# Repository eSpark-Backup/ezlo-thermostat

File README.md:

# Ezlo - Thermostat
Ezlo Thermostat is an enhanced version of the Centralite Thermostat product that gives user the exciting feature of a smart thermostat system accompanied by the amazing MiOS dashboard in a tablet screen on the thermostat product that greatly adds to the overall experience and UI.
The thermostat is accompanied by a separate small PCB that mounts the infineon Radar sensor for presence and occupancy sensing.

## Project Requirements v2.0
The schematic design was already finished and tested to run successfully with the existing features. The new version will have the following features in addition to existing features both of which are listed below:
* The thermostat should be based off of and ESP32-S3 based module.
* The thermostat should have a separate PCB that mounts the Infineon Radar sensor.
* The thermostat will have 2 x cameras. The datasheet of the cameras are attached. [HK-2385^M2385-706(7731)  Camera Spec 承认书.pdf](https://github.com/eSpark-Consultants/ezlo-thermostat/files/11762271/HK-2385.M2385-706.7731.Camera.Spec.pdf). According to client, the cameras are intended to be connected directly with the tablet but a thorough study of the attached camera module is necessary to confirm this. There will be 2 x camera modules used in thermostat design.
* The thermostat will have an android 7" tablet for displaying the MiOS dashboard. The tablet datasheet is attached.[LCD Display Spec 7inch.pdf](https://github.com/eSpark-Consultants/ezlo-thermostat/files/11762286/LCD.Display.Spec.7inch.pdf). Attached further are the dxf drawings of the LCD (not confirmed. [F0753_V1.1-2D(1) PCB.zip](https://github.com/eSpark-Consultants/ezlo-thermostat/files/11762290/F0753_V1.1-2D.1.PCB.zip)
* The thermostat will have basic amplitude detection using 1 or 2 microphones (as suitable)
* The thermostat will have gesture recognition capability. A module is suggested by client which is **GY- PAJ7620U2** but open to better options. The selection should prioritize cost effectiveness and available firmware support. 
* Another point of discussion is if the internet / WiFi goes down, what is the most feasible means of communication between Tablet and on board ESP32? A few options are; ESP32 as Web Server; BLE; Wired link between tablet and ESP32.

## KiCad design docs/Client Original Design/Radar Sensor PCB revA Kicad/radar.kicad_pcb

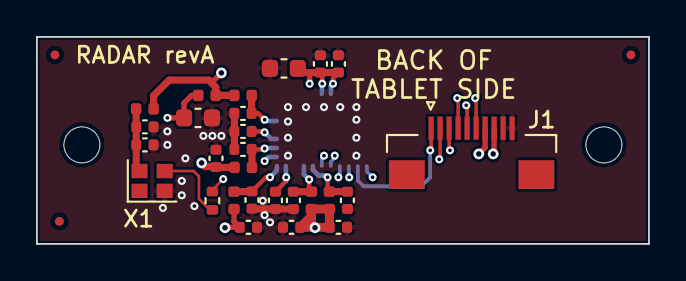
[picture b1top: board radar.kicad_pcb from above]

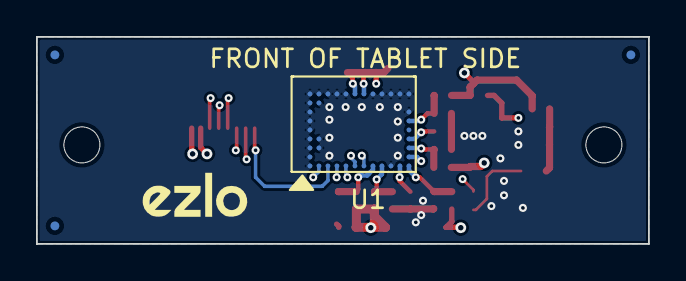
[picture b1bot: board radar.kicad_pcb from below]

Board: 4 copper layers, 34.0 x 11.5 mm, 37 parts (5 on the bottom side), 19 nets.

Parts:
C1: 0.01uF; C_0402_1005Metric
C2, C5, C6, C7, C8, C9, C10, C12: 1uF; C_0402_1005Metric
C3: 0.47uF; C_0402_1005Metric
C4: 0.1uF; C_0402_1005Metric
C11, C14: 22uF; C_0603_1608Metric
C13, C15, C16, C17: 10uF; C_0402_1005Metric
FB1, FB2, FB3, FB4, FB5, FB6, FB7: BLM15PD121SN1B; L_0402_1005Metric
FID1, FID2, FID3, FID4, FID5, FID6: Fiducial; Fiducial_0.5mm_Mask1mm
H1, H2: MountingHole; MountingHole_2mm
J1: Conn_01x10; AFC01-S10FCC-00_1x10_P0.5mm_Horizontal
R1: 150R; R_0402_1005Metric
U1: BGT60TR13C; PG-VF2BGA40-1
V1: EZLO_LOGO; Logo Ezlo_S
X1: 80MHz; Crystal_SMD_2016-4Pin_2.0x1.6mm

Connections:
1V8_SENSOR: C13.1, C15.1, C17.1, FB1.2, FB2.2, FB3.2, FB5.2, FB6.2, FB7.2, J1.7
3V3_SENSOR: C16.1, FB4.2, J1.8
/BGT_CLK: J1.5, U1.B1 (CLK)
/BGT_CS: J1.6, U1.G1 (~CS)
/BGT_IRQ: J1.1, U1.C1 (IRQ)
/BGT_MISO: J1.3, U1.E1 (DO)
/BGT_MOSI: J1.2, U1.D1 (DI)
/BGT_RST: J1.4, U1.F1 (DIO3)
/OSC_80M: R1.1, U1.M2 (OSC_CLK)
/OSC_OUT: R1.2, X1.3 (OUT)
/VAREF: C3.1, U1.L1 (VAREF)
/VDD_A: C4.1, FB3.1, U1.J1 (VDDA)
/VDD_D: C5.1, FB2.1, U1.H1 (VDDD)
/VDD_LF: C6.1, FB4.1, U1.M3 (VDDLF)
/VDD_OSC: C1.1, C2.1, FB1.1, X1.4 (VCC)
/VDD_PLL: C9.1, C11.1, FB6.1, U1.M4 (VDDPLL)
/VDD_RF: C7.1, C10.1, C12.1, C14.1, FB7.1, U1.F9 (VDDRF), U1.G9 (VDDRF), U1.M1 (VDDRF)
/VDD_VCO: C8.1, FB5.1, U1.M6 (VDDVCO)
GND: C1.2, C2.2, C3.2, C4.2, C5.2, C6.2, C7.2, C8.2, C9.2, C10.2, C11.2, C12.2, C13.2, C14.2, C15.2, C16.2, C17.2, J1.9, J1.10, U1.A1 (VSSD), U1.A2 (VSSD), U1.A3 (VSSRF), U1.A4 (VSSRF), U1.A5 (VSSRF), U1.A6 (VSSRF), U1.A7 (VSSRF), U1.A8 (VSSRF), U1.A9 (VSSRF), U1.B3 (VSSRF), U1.B4 (VSSRF), U1.B8 (VSSRF), U1.B9 (VSSRF), U1.C9 (VSSRF), U1.D9 (VSSRF), U1.E9 (VSSRF), U1.H9 (VSSRF), U1.J9 (VSSRF), U1.K1 (VSSA), U1.K9 (VSSRF), U1.L9 (VSSRF), U1.M7 (VSSRF), U1.M9 (VSSRF), X1.2 (GND)

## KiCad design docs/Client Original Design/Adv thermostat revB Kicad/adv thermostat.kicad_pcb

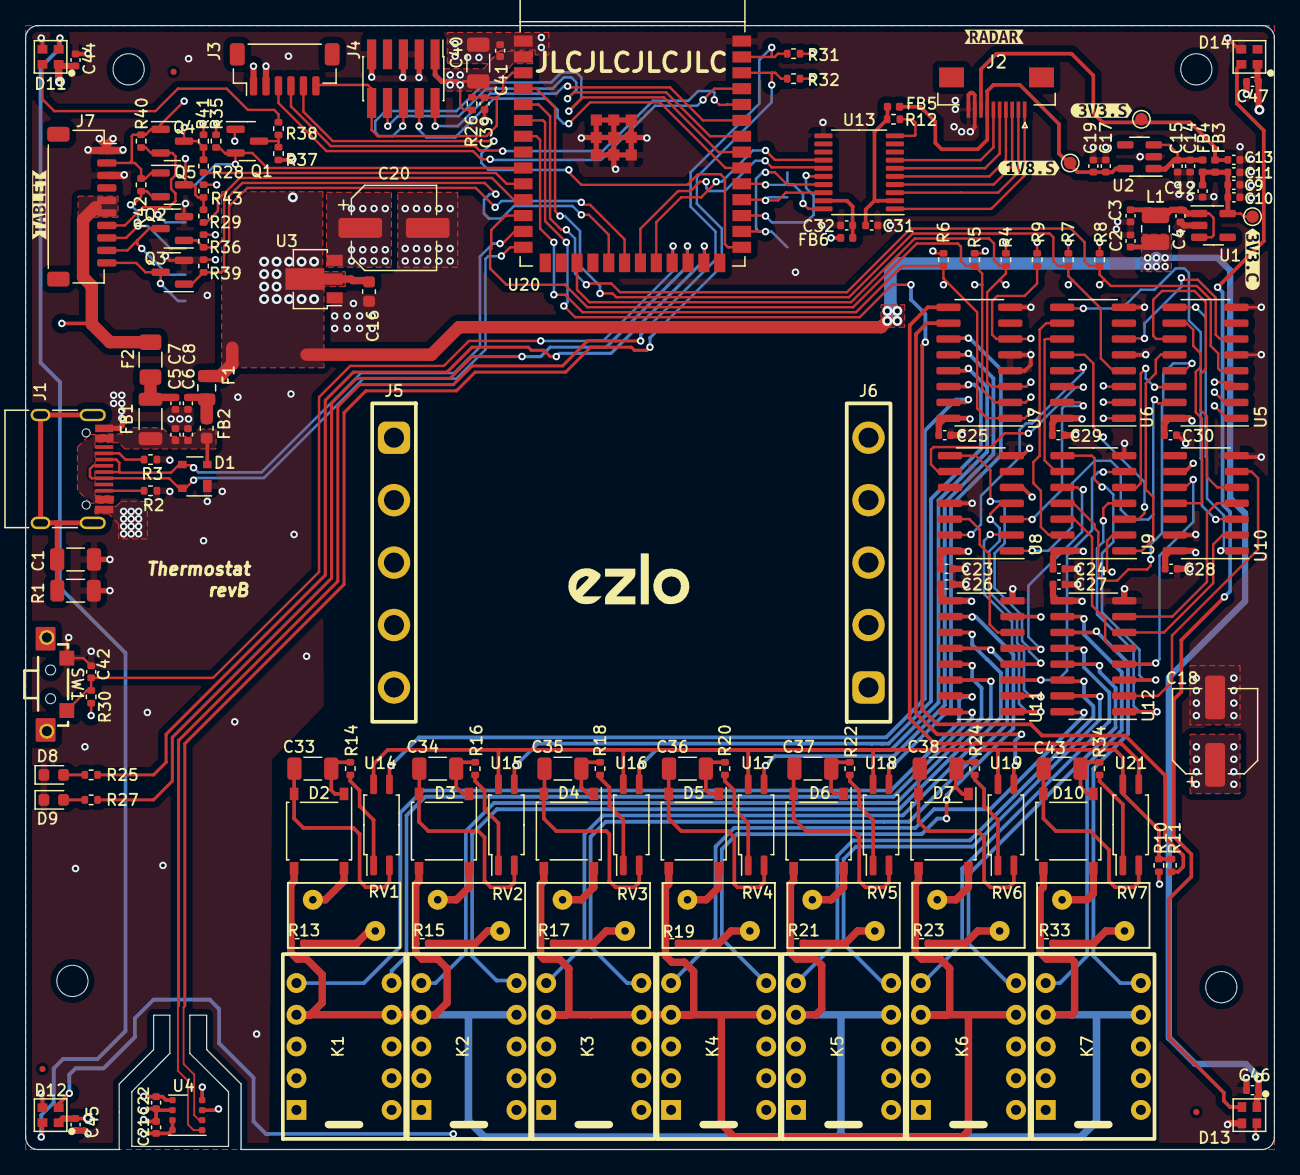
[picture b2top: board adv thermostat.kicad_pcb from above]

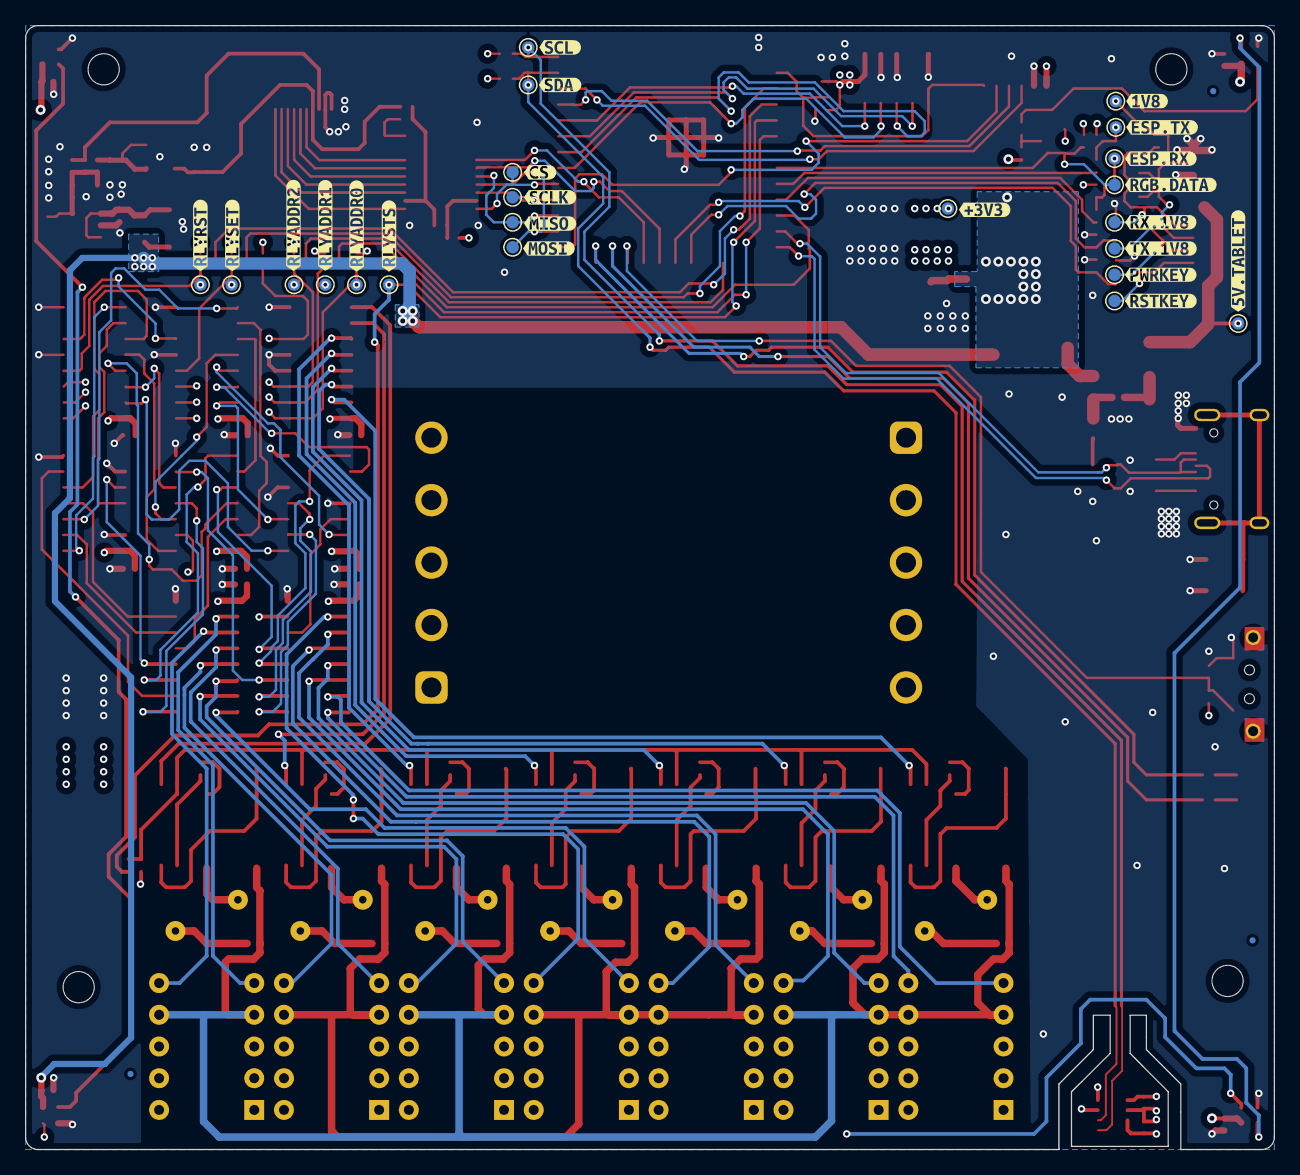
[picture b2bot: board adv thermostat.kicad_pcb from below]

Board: 4 copper layers, 100.0 x 90.0 mm, 224 parts (47 on the bottom side), 159 nets.

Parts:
C1: 4.7nF; C_1206_3216Metric
C2, C3, C10, C14, C19: 10uF; C_0402_1005Metric
C4, C7, C8, C9, C11, C12, C13, C15, C17, C21, C22, C23, C24, C25, C26, C27, C28, C29, C30, C31, C32, C41, C42, C44, C45, C46, C47: 0.1uF; C_0402_1005Metric
C5, C6: 0.01uF; C_0402_1005Metric
C16: 10uF; C_0603_1608Metric
C18, C20: 100uF; CP_Elec_6.3x5.8
C33, C34, C35, C36, C37, C38, C43: 0.22uF; C_1206_3216Metric
C39: 1uF; C_0402_1005Metric
C40: 22uF; C_1206_3216Metric
D1: SP0503BAHT; SOT-143
D2, D3, D4, D5, D6, D7, D10: ABS2; Diode_Bridge_Diotec_ABS
D8: LED_RED; LED_0603_1608Metric
D9: LED_GREEN; LED_0603_1608Metric
D11, D12, D13, D14: SK6812-EC20; sk6812-2020
F1: 1A; Fuse_0805_2012Metric
F2: 2A; Fuse_1206_3216Metric
FB1: BLM31PG121SN1L; L_1206_3216Metric
FB2: BLM18SG121TN1D; L_0603_1608Metric
FB3, FB4, FB5, FB6: BLM15PD121SN1B; L_0402_1005Metric
FID1, FID2, FID3, FID4, FID5, FID6: Fiducial; Fiducial_0.5mm_Mask1mm
H1, H2, H3, H4: MountingHole; MountingHole_2.5mm
J1: USB_C_Receptacle_USB2.0; USB_C_Receptacle_HRO_TYPE-C-31-M-12
J2: Conn_01x10; AFC01-S10FCC-00_1x10_P0.5mm_Horizontal
J3: VoltLink_target; VoltLink-vertical
J4: ESP32_JTAG_10; PinHeader_2x05_P1.27mm_Vertical_SMD
J5: Clamp-Terminal-A; PinHeader_1x05_P5.00mm_Vertical
J6: Clamp-Terminal-B; PinHeader_1x05_P5.00mm_Vertical
J7: Tablet_Conn_01x10; JST_SH_SM10B-SRSS-TB_1x10-1MP_P1.00mm_Horizontal
K1, K2, K3, K4, K5, K6, K7: EA2-3TNU
L1: 10uH; L_1008_2520Metric
Q1, Q2, Q3, Q4, Q5: Si2302CDS; SOT-23
R1: 1M; R_1206_3216Metric
R2, R3: 5K1; R_0402_1005Metric
R4, R5, R6, R7, R8, R9, R10, R26, R30, R36, R39: 220K; R_0402_1005Metric
R11: 47K; R_0402_1005Metric
R12: 0R; R_0402_1005Metric
R13, R15, R17, R19, R21, R23, R33: 47R; R_0402_1005Metric
R14, R16, R18, R20, R22, R24, R34: 100K; R_0402_1005Metric
R25, R27, R38: 1K; R_0402_1005Metric
R28, R29: 22R; R_0402_1005Metric
R31, R32: 4K7; R_0402_1005Metric
R35, R37, R40, R41, R42, R43: 10K; R_0402_1005Metric
RV1, RV2, RV3, RV4, RV5, RV6, RV7: ERZ-V07D680; RV_Disc_D9mm_W5.2mm_P5mm
SW1: USER; Switch_YTS-B003-2A
TP1: 3V3_C; TestPoint_Pad_D1.0mm
TP2: 3V3_S; TestPoint_Pad_D1.0mm
TP3: 1V8_S; TestPoint_Pad_D1.0mm
TP4: 3V3; TestPoint_Pad_D1.0mm
TP5: ADDR0; TestPoint_Pad_D1.0mm
TP6: ADDR1; TestPoint_Pad_D1.0mm
TP7: ADDR2; TestPoint_Pad_D1.0mm
TP8: RSET; TestPoint_Pad_D1.0mm
TP9: RRST; TestPoint_Pad_D1.0mm
TP10: RSTS; TestPoint_Pad_D1.0mm
TP11: SCL; TestPoint_Pad_D1.0mm
TP12: SDA; TestPoint_Pad_D1.0mm
TP13: MOSI; TestPoint_Pad_D1.0mm
TP14: MISO; TestPoint_Pad_D1.0mm
TP15: SCLK; TestPoint_Pad_D1.0mm
TP16: CS; TestPoint_Pad_D1.0mm
TP17: RGB; TestPoint_Pad_D1.0mm
TP18: 5V_TABLET; TestPoint_Pad_D1.0mm
TP19: 1V8; TestPoint_Pad_D1.0mm
TP20: PWRKEY; TestPoint_Pad_D1.0mm
TP21: RSTKEY; TestPoint_Pad_D1.0mm
TP22: RXA; TestPoint_Pad_D1.0mm
TP23: RXB; TestPoint_Pad_D1.0mm
TP24: TXA; TestPoint_Pad_D1.0mm
TP25: TXB; TestPoint_Pad_D1.0mm
U1: XC6228D332VR-G; SOT-23-5
U2: XC6228D182VR-G; SOT-23-5
U3: LR1107; SOT-89-3
U4: BME680; Bosch_LGA-8_3x3mm_P0.8mm_ClockwisePinNumbering
U5, U6, U7: 74LVC138A; SOIC-16_3.9x9.9mm_P1.27mm
U8, U9, U10: 74LV14; SOIC-14_3.9x8.7mm_P1.27mm
U11, U12: ULN2003A; SOIC-16_3.9x9.9mm_P1.27mm
U13: TXS0108EPWR; TSSOP-20_4.4x6.5mm_P0.65mm
U14, U15, U16, U17, U18, U19, U21: OR-3H7B-TP-G; SOIC-4_4.55x2.6mm_P1.27mm
U20: ESP32-S3-WROOM-1
V1: EZLO_LOGO; Logo Ezlo_M
kibuzzard-6319A1D4: G***; kibuzzard-6319A1D4
kibuzzard-6319A1F9: G***; kibuzzard-6319A1F9
kibuzzard-6319A2D8: G***; kibuzzard-6319A2D8
kibuzzard-6319A18B: G***; kibuzzard-6319A18B
kibuzzard-6319A20C: G***; kibuzzard-6319A20C
kibuzzard-6319A21E: G***; kibuzzard-6319A21E
kibuzzard-6319A206: G***; kibuzzard-6319A206
kibuzzard-6319A232: G***; kibuzzard-6319A232
kibuzzard-6319A321: G***; kibuzzard-6319A321
kibuzzard-6319AA0F: G***; kibuzzard-6319AA0F
kibuzzard-6319AA3B: G***; kibuzzard-6319AA3B
kibuzzard-6319AA4A: G***; kibuzzard-6319AA4A
kibuzzard-6319AA9A: G***; kibuzzard-6319AA9A
kibuzzard-6319AA19: G***; kibuzzard-6319AA19
kibuzzard-6319AA29: G***; kibuzzard-6319AA29
kibuzzard-6319AA54: G***; kibuzzard-6319AA54
kibuzzard-6319AA76: G***; kibuzzard-6319AA76
kibuzzard-6319AAA5: G***; kibuzzard-6319AAA5
kibuzzard-6319AAAF: G***; kibuzzard-6319AAAF
kibuzzard-6319AABA: G***; kibuzzard-6319AABA
kibuzzard-6319AAC1: G***; kibuzzard-6319AAC1
kibuzzard-63199E43: G***; kibuzzard-63199E43
kibuzzard-63199EB3: G***; kibuzzard-63199EB3
kibuzzard-63199ED2: G***; kibuzzard-63199ED2
kibuzzard-63199EEF: G***; kibuzzard-63199EEF
kibuzzard-63199F83: G***; kibuzzard-63199F83
kibuzzard-639863C7: G***; kibuzzard-639863C7

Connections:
1V8_SENSOR: C17.1, C19.1, FB5.2, J2.7, TP3.1, U2.5 (VOUT)
3V3_SENSOR: C13.1, FB3.2, J2.8, TP2.1
+1V8: J7.2, Q4.1 (G), Q5.1 (G), R40.1, R42.1, TP19.1
+3V3: C18.1, C20.1, C21.2, C22.1, C23.1, C24.1, C25.1, C26.1, C27.1, C28.1, C29.1, C30.1, C40.2, C41.2, FB6.1, J3.1 (3V3), J4.1 (VTref), K1.1, K1.10, K2.1, K2.10, K3.1, K3.10, K4.1, K4.10, K5.1, K5.10, K6.1, K6.10, K7.1, K7.10, Q1.1 (G), R4.1, R5.1, R6.1, R7.1, R8.1, R9.1, R10.1, R26.2, R30.2, R31.2, R32.2, R35.1, R41.1, R43.1, TP4.1, U3.3 (VOUT), U4.2 (CSB), U4.5 (SDO), U4.6 (VDDIO), U4.8 (VDD), U5.16 (VCC), U6.16 (VCC), U7.16 (VCC), U8.14 (3.3V), U9.14 (3.3V), U10.14 (3.3V), U11.9 (COM), U12.9 (COM), U20.2 (3V3)
+5V: C2.1, C16.1, C44.1, C45.1, C46.1, C47.1, D11.1 (VDD), D12.1 (VDD), D13.1 (VDD), D14.1 (VDD), F1.1, L1.1, R37.1, U3.2 (VIN)
/ESP32/CS: TP16.1, U13.20 (B1), U20.31 (GPIO38)
/ESP32/EN: C39.1, J3.6 (EN), J4.10 (~RESET), R26.1, U20.3 (EN)
/ESP32/ESP_RXD: Q5.3 (D), R29.1, R43.2, TP25.1
/ESP32/ESP_TXD: Q4.3 (D), R28.1, R41.2, TP23.1
/ESP32/GPIO11: Q2.1 (G), R36.1, U20.19 (GPIO11)
/ESP32/GPIO12: Q3.1 (G), R39.1, U20.20 (GPIO12)
/ESP32/GPIO16: Q1.2 (S), R35.2, TP17.1, U20.9 (GPIO16)
/ESP32/GPIO21: C42.1, R30.1, SW1.1, U20.23 (GPIO21)
/ESP32/GPIO47: R27.1, U20.24 (GPIO47)
/ESP32/GPIO48: R25.1, U20.25 (GPIO48)
/ESP32/IO0: J3.5 (IO0), U20.27 (GPIO0/BOOT)
/ESP32/MISO: TP14.1, U13.16 (B4), U20.29 (GPIO36)
/ESP32/MOSI: TP13.1, U13.17 (B3), U20.28 (GPIO35)
/ESP32/RXD: J3.4 (RXD), U20.36 (U0RXD/GPIO44)
/ESP32/SCL: R31.1, TP11.1, U4.4 (SCK), U20.39 (GPIO1)
/ESP32/SCLK: TP15.1, U13.18 (B2), U20.30 (GPIO37)
/ESP32/SDA: R32.1, TP12.1, U4.3 (SDI), U20.38 (GPIO2)
/ESP32/TCK: J4.4 (TCK), U20.32 (TCK/GPIO39)
/ESP32/TDI: J4.8 (TDI), U20.34 (TDI/GPIO41)
/ESP32/TDO: J4.6 (TDO), U20.33 (TDO/GPIO40)
/ESP32/TMS: J4.2 (TMS), U20.35 (TMS/GPIO42)
/ESP32/TXD: J3.3 (TXD), U20.37 (U0TXD/GPIO43)
/Level shifter/A1: J2.1, U13.1 (A1)
/Level shifter/A2: J2.2, U13.3 (A2)
/Level shifter/A3: J2.3, U13.4 (A3)
/Level shifter/A4: J2.4, U13.5 (A4)
/Level shifter/A5: J2.5, U13.6 (A5)
/Level shifter/A6: J2.6, U13.7 (A6)
/Level shifter/B5: U13.15 (B5), U20.21 (GPIO13)
/Level shifter/B6: U13.14 (B6), U20.22 (GPIO14)
/Level shifter/SPI_OE: R12.1, U13.10 (OE)
/Level shifter/VCCA: C31.1, FB5.1, R12.2, U13.2 (VCCA)
/Level shifter/VCCB: C32.1, FB6.2, U13.19 (VCCB)
/Output/24VAC: D2.3, D3.3, D6.3, D10.3, J5.4, K1.4 (O1), K1.7 (O2), K2.4 (O1), K2.7 (O2), K5.4 (O1), K5.7 (O2), K7.4 (O1), K7.7 (O2), R13.2, R15.2, R21.2, R33.2
/Output/E3: R9.2, U5.6 (E3), U6.6 (E3), U7.6 (E3)
/Output/RELAYSTSN0: U7.15 (O0), U14.3
/Output/RELAYSTSN1: U7.14 (O1), U15.3
/Output/RELAYSTSN2: U7.13 (O2), U16.3
/Output/RELAYSTSN3: U7.12 (O3), U17.3
/Output/RELAYSTSN4: U7.11 (O4), U18.3
/Output/RELAYSTSN5: U7.10 (O5), U19.3
/Output/RELAYSTSN6: U7.9 (O6), U21.3
/Output/RH: D4.3, D5.3, D7.3, J5.5, K3.4 (O1), K3.7 (O2), K4.4 (O1), K4.7 (O2), K6.4 (O1), K6.7 (O2), R17.2, R19.2, R23.2
/Output/RLYADDR0: R6.2, TP5.1, U5.1 (A0), U6.1 (A0), U7.1 (A0), U20.7 (GPIO7)
/Output/RLYADDR1: R5.2, TP6.1, U5.2 (A1), U6.2 (A1), U7.2 (A1), U20.12 (GPIO8)
/Output/RLYADDR2: R4.2, TP7.1, U5.3 (A2), U6.3 (A2), U7.3 (A2), U20.17 (GPIO9)
/Output/RLYR0: K1.6, U11.16 (O1)
/Output/RLYR1: K2.6, U11.14 (O3)
/Output/RLYR2: K3.6, U11.12 (O5)
/Output/RLYR3: K4.6, U11.10 (O7)
/Output/RLYR4: K5.6, U12.15 (O2)
/Output/RLYR5: K6.6, U12.13 (O4)
/Output/RLYR6: K7.6, U12.11 (O6)
/Output/RLYRST: R8.2, TP9.1, U5.4 (E1), U20.5 (GPIO5)
/Output/RLYRSTN0: U5.15 (O0), U8.1
/Output/RLYRSTN1: U5.14 (O1), U9.5
/Output/RLYRSTN2: U5.13 (O2), U9.11
/Output/RLYRSTN3: U5.12 (O3), U9.1
/Output/RLYRSTN4: U5.11 (O4), U10.5
/Output/RLYRSTN5: U5.10 (O5), U10.11
/Output/RLYRSTN6: U5.9 (O6), U10.1
/Output/RLYS0: K1.5, U11.15 (O2)
/Output/RLYS1: K2.5, U11.13 (O4)
/Output/RLYS2: K3.5, U11.11 (O6)
/Output/RLYS3: K4.5, U12.16 (O1)
/Output/RLYS4: K5.5, U12.14 (O3)
/Output/RLYS5: K6.5, U12.12 (O5)
/Output/RLYS6: K7.5, U12.10 (O7)
/Output/RLYSET: R7.2, TP8.1, U6.4 (E1), U20.4 (GPIO4)
/Output/RLYSETN0: U6.15 (O0), U8.3
/Output/RLYSETN1: U6.14 (O1), U8.9
/Output/RLYSETN2: U6.13 (O2), U8.13
/Output/RLYSETN3: U6.12 (O3), U9.3
/Output/RLYSETN4: U6.11 (O4), U9.9
/Output/RLYSETN5: U6.10 (O5), U9.13
/Output/RLYSETN6: U6.9 (O6), U10.3
/Output/RLYSTS: R11.2, TP10.1, U20.6 (GPIO6)
/Output/RLY_R0: U8.2, U11.1 (I1)
/Output/RLY_R1: U9.6, U11.3 (I3)
/Output/RLY_R2: U9.10, U11.5 (I5)
/Output/RLY_R3: U9.2, U11.7 (I7)
/Output/RLY_R4: U10.6, U12.2 (I2)
/Output/RLY_R5: U10.10, U12.4 (I4)
/Output/RLY_R6: U10.2, U12.6 (I6)
/Output/RLY_S0: U8.4, U11.2 (I2)
/Output/RLY_S1: U8.8, U11.4 (I4)
/Output/RLY_S2: U8.12, U11.6 (I6)
/Output/RLY_S3: U9.4, U12.1 (I1)
/Output/RLY_S4: U9.8, U12.3 (I3)
/Output/RLY_S5: U9.12, U12.5 (I5)
/Output/RLY_S6: U10.4, U12.7 (I7)
/Output/relay0/COM: J6.5, K1.2 (C1), K1.9 (C2), K2.2 (C1), K2.9 (C2), K3.2 (C1), K3.9 (C2), K4.2 (C1), K4.9 (C2), K5.2 (C1), K5.9 (C2), K6.2 (C1), K6.9 (C2), K7.2 (C1), K7.9 (C2)
/Output/relay0/RELAY_O: D2.4, J5.1, K1.3 (P1), K1.8 (P2), RV1.1
/Output/relay0/RELAY_STS: R10.2, R11.1, U14.4, U15.4, U16.4, U17.4, U18.4, U19.4, U21.4
/Output/relay1/RELAY_O: D3.4, J5.2, K2.3 (P1), K2.8 (P2), RV2.1
/Output/relay2/RELAY_O: D4.4, J5.3, K3.3 (P1), K3.8 (P2), RV3.1
/Output/relay3/RELAY_O: D5.4, J6.1, K4.3 (P1), K4.8 (P2), RV4.1
/Output/relay4/RELAY_O: D6.4, J6.2, K5.3 (P1), K5.8 (P2), RV5.1
/Output/relay5/RELAY_O: D7.4, J6.3, K6.3 (P1), K6.8 (P2), RV6.1
/Output/relay6/RELAY_O: D10.4, J6.4, K7.3 (P1), K7.8 (P2), RV7.1
/Power-Interface/3V3_CLEAN: C9.1, C10.1, C11.1, C12.1, FB3.1, FB4.1, TP1.1, U1.5 (VOUT)
/Power-Interface/3V3_LDO1V8: C14.1, C15.1, FB4.2, U2.1 (VIN), U2.3 (CE)
/Power-Interface/5V_CLEAN: C3.1, C4.1, L1.2, U1.1 (VIN), U1.3 (CE)
/Power-Interface/CC1: J1.A5 (CC1), R3.1
/Power-Interface/CC2: J1.B5 (CC2), R2.1
/Power-Interface/USB_D_N: D1.3 (K), J1.A7 (D-), J1.B7 (D-), U20.13 (GPIO19/USB_D-)
/Power-Interface/USB_D_P: D1.4 (K), J1.A6 (D+), J1.B6 (D+), U20.14 (GPIO20/USB_D+)
/Power-Interface/VBUS: C5.1, C6.1, D1.2 (K), FB1.1, FB2.1, J1.A4 (VBUS), J1.A9 (VBUS), J1.B4 (VBUS), J1.B9 (VBUS)
/misc/5V_TABLET: F2.1, J7.5, J7.6, TP18.1
/misc/DIN1: D11.4 (DIN), R38.2
/misc/DIN2: D11.2 (DOUT), D12.4 (DIN)
/misc/DIN3: D12.2 (DOUT), D13.4 (DIN)
/misc/DIN4: D13.2 (DOUT), D14.4 (DIN)
GND: C1.2, C2.2, C3.2, C4.2, C5.2, C6.2, C7.2, C8.2, C9.2, C10.2, C11.2, C12.2, C13.2, C14.2, C15.2, C16.2, C17.2, C18.2, C19.2, C20.2, C21.1, C22.2, C23.2, C24.2, C25.2, C26.2, C27.2, C28.2, C29.2, C30.2, C31.2, C32.2, C39.2, C40.1, C41.1, C42.2, C44.2, C45.2, C46.2, C47.2, D1.1 (A), D8.1 (K), D9.1 (K), D11.3 (VSS), D12.3 (VSS), D13.3 (VSS), D14.3 (VSS), J1.A1 (GND), J1.A12 (GND), J1.B1 (GND), J1.B12 (GND), J2.9, J2.10, J3.2 (GND), J4.3 (GND), J4.5 (GND), J4.9 (GNDDetect), J7.1, J7.3, Q2.2 (S), Q3.2 (S), R1.2, R2.2, R3.2, R36.2, R39.2, SW1.2, U1.2 (GND), U2.2 (GND), U3.1 (GND), U4.1 (GND), U4.7 (GND), U5.5 (E2), U5.8 (GND), U6.5 (E2), U6.8 (GND), U7.4 (E1), U7.5 (E2), U7.8 (GND), U8.5, U8.7 (GND), U8.11, U9.7 (GND), U10.7 (GND), U10.9, U10.13, U11.8 (GND), U12.8 (GND), U13.11 (GND), U20.1 (GND), U20.40 (GND), U20.41 (GND)
unnamed: C1.1, J1.S1 (SHIELD), R1.1
unnamed: C7.1, F2.2, FB1.2
unnamed: C8.1, F1.2, FB2.2
unnamed: C33.1, D2.1 (+), R14.1
unnamed: C33.2, D2.2 (-), U14.2
unnamed: C34.1, D3.1 (+), R16.1
unnamed: C34.2, D3.2 (-), U15.2
unnamed: C35.1, D4.1 (+), R18.1
unnamed: C35.2, D4.2 (-), U16.2
unnamed: C36.1, D5.1 (+), R20.1
unnamed: C36.2, D5.2 (-), U17.2
unnamed: C37.1, D6.1 (+), R22.1
unnamed: C37.2, D6.2 (-), U18.2
unnamed: C38.1, D7.1 (+), R24.1
unnamed: C38.2, D7.2 (-), U19.2
unnamed: C43.1, D10.1 (+), R34.1
unnamed: C43.2, D10.2 (-), U21.2
unnamed: D8.2 (A), R25.2
unnamed: D9.2 (A), R27.2
unnamed: Q1.3 (D), R37.2, R38.1
unnamed: R13.1, RV1.2
unnamed: R14.2, U14.1
unnamed: R15.1, RV2.2
unnamed: R16.2, U15.1
unnamed: R17.1, RV3.2
unnamed: R18.2, U16.1
unnamed: R19.1, RV4.2
unnamed: R20.2, U17.1
unnamed: R21.1, RV5.2
unnamed: R22.2, U18.1
unnamed: R23.1, RV6.2
unnamed: R24.2, U19.1
unnamed: R28.2, U20.10 (GPIO17)
unnamed: R29.2, U20.11 (GPIO18)
unnamed: R33.1, RV7.2
unnamed: R34.2, U21.1
PWRKEY: J7.9, Q2.3 (D), TP20.1
RSTKEY: J7.10, Q3.3 (D), TP21.1
RX_1V8: J7.7, Q4.2 (S), R40.2, TP22.1
TX_1V8: J7.8, Q5.2 (S), R42.2, TP24.1

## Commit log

2022-12-19 Client's original design pushed
2022-12-19 #1 In progress
2022-12-27 #2 Complete
2022-12-27 Complete
2022-12-27 #3 In progress
2022-12-28 #3 Completed.
2022-12-28 #4 Completed.
2022-12-29 #4 Layer stackup set and Fresh deliverables generated
2022-12-29 #1 Complete
2022-12-30 #6 In progress
2023-01-02 #6 PCB parts Placement completed, Routing in Progress
2023-01-02 #7 In progress
2023-01-03 #8 Routing in Progress
2023-01-06 #6 Routing completed
2023-01-06 #9 In-Progress.
2023-01-07 #9 Done.
2023-01-07 #10 Done.
2023-01-12 #11 In-progress.
2023-01-13 #12 correction done in Radar
2023-01-13 #11 Routing in Progress
2023-01-13 #13 Done.
2023-01-13 #4 Done.
2023-01-13 @MarsVirgo KICAD Files Add kr di han Repo me.
2023-01-13 #4 Fresh Deliverables Created.
2023-01-13 #4 Fresh Deliverables.
2023-01-15 #11 Completed.
2023-01-16 #9 Footprint confirmed#10 Fresh Deliverables generated
2023-01-16 #9 changes done after footprint changes of relay and varistor #10 fresh deliverables generated
2023-01-17 created .gitignore
2023-01-17 #14 Clamp Terminal added. Capacitors adjusted
2023-01-17 #11 and #10 Done.
2023-01-18 #12 C7 updated accordingly and Fresh Deliverables generated
2023-01-18 #10 and #11 both done.
2023-01-19 Schematic reformatting
2023-01-19 Old PCB removed
2023-01-19 pushed .gitignore
2023-01-19 removed extras
2023-01-19 generated design PDF
2023-06-15 Project requirements for v2.0 of thermostat
2023-06-20 #17 Initial Design push with Advanced version files
2023-06-26 #17 Schematic Changes Done
2023-06-27 #16 J2 Connector changed - MIC - Gesture connections added
2023-06-27 #16 MIC - Gesture sensor added - Radar Advance
2023-06-27 #16 J2 Footprint updated - 3.3V Regulator changed
2023-06-27 #16 FPC connector footprint updated - Radar
2023-07-03 #7 eSpark BOM updated.
2023-07-03 #18 Design Completed. Stackup needs to be verified
2023-07-04 #16 NetLabel changed from VIN_3V3 to 5V_Clean
2023-07-04 #19 In Progress
2023-07-04 #18 Matched PCB Stackup as in Client's KiCad file.
2023-07-06 #19 Design is ready.
2023-07-07 #21 In progress
2023-07-12 #21 In-progress
2023-07-17 #21 Finishing and some component placement verification remaining
2023-07-17 #22 Review Done: Corrections in Routing.
2023-07-18 #21 Design is ready as per the current schematic.
2023-07-19 #22 U2 updated in PCB
2023-07-20 #22 Fresh Deliverables created. Version no. added in Design files.
2023-07-20 #22 Fresh Deliverables after Text modification.
2023-07-20 #22 Updated Centroid File
2023-07-24 Folder hierarchy updated
2023-07-25 #19 Latest step file for Main PCB.
2023-07-25 #18 #22 Latest Step file of Radar PCB
2023-07-25 #25 Radar Client BOM added
2023-07-25 #25 Thermostate BOM Added
2023-07-26 #18 #22 Crystal X1 footprint updated
2023-07-26 #25 Peripheral Added in BOM
2023-07-26 #19 #24 U14 (TSSOP-20) Footprint updated (Pads size increased).
2023-07-26 #18 #22 Added MIC Port text and reviewed before generating deliverables
2023-07-26 #18 #22 Complete deliverables generated
2023-07-26 #22 Project file
2023-07-26 #19 #24 Some improvements in the design
2023-07-26 #24 Complete deliverables generated
2023-09-25 Basic Thermostat moved to individual folder
2023-09-25 #17 J5 Header replace.
2023-09-25 #17 PDF Added. Designators updated
2023-09-27 #20 #17 R20 resistor changed to 33 ohm. Rest is clear
2023-10-03 #21 Connector J3 and J2 changes done in PCB. J3 will be exactly aligned with the LCD's step file.
2023-10-03 #21 Polygon was shelved. Changes done.
2023-10-04 #21 Step file generated
2023-11-07 TN Display Datasheet, Addresses, Sample Code
